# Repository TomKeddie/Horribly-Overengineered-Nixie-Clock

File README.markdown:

# Horribly Overengineered Nixie Clock

This is a "horribly overengineered" Nixie clock as the "clock" part could have been achieved far cheaper
and far easier. However, the end result (that there is an actual physical clock) is merely a side effect;
the main motivation for me was to use this project as means to learn something new. To this end, I've used
a fairly expensive ARM microcontroller and the mainboard also includes both USB and Ethernet connectivity.

There are two PCBs in this project: a driver board housing two Nixie tubes with their corresponding drivers
and a mainboard with the uC and other circuitry. The driver board is designed to fit into the 5x5 cm limit
and the mainboard fits the 5x10 cm limit of ITead Studio/Seeed Studio. A full kit with 6 digits would consist
of one mainboard PCB and three driver PCBs.

(The firmware will appear here as soon as there is something usable.)

## BOM

The key components are:

  * ИН-12 Nixie tubes
  * К155ИД1 drivers
  * [Taylor Electronics HVPS-V](http://www.tayloredge.com/storefront/SmartNixie/PSU/index.html) high voltage power supply
  * [NXP LPC1764](http://ics.nxp.com/products/lpc1000/lpc17xx/~LPC1764/) ARM Cortex-M3 microcontroller

Rev A:
  * [Micrel KSZ8001L](http://www.micrel.com/page.do?page=product-info/fastether_trans.jsp) Ethernet PHY

Rev B:
 
  * [Micrel MIC4680](http://micrel.com/index.php/en/component/joodb/article/41-step-down-internal-switches/24-mic4680.html) buck regulator
  * [Micrel KSZ8051RNL](http://micrel.com/index.php/en/component/joodb/article/13-phys/10-ksz8051rnl.html) Ethernet PHY

## Truth table for module

Note that for ease of routing the truth table doesn't match 74(1)41/K155ID1:

<table>
  <tr><th>Num</th> <th>A</th> <th>B</th> <th>C</th> <th>D</th></tr>
  <tr><td>0</td><td>H</td><td>L</td><td>H</td><td>L</td></tr>
  <tr><td>1</td><td>H</td><td>L</td><td>L</td><td>H</td></tr>
  <tr><td>2</td><td>L</td><td>H</td><td>H</td><td>L</td></tr>
  <tr><td>3</td><td>H</td><td>H</td><td>H</td><td>L</td></tr>
  <tr><td>4</td><td>L</td><td>H</td><td>L</td><td>L</td></tr>
  <tr><td>5</td><td>H</td><td>H</td><td>L</td><td>L</td></tr>
  <tr><td>6</td><td>L</td><td>L</td><td>H</td><td>L</td></tr>
  <tr><td>7</td><td>L</td><td>L</td><td>L</td><td>H</td></tr>
  <tr><td>8</td><td>L</td><td>L</td><td>L</td><td>L</td></tr>
  <tr><td>9</td><td>H</td><td>L</td><td>L</td><td>L</td></tr>
</table>

## Errata for Rev A

  * SWDCLK is not routed to JTAG. Oops.
  * P0[28] does not have an external pull-up. Note to self: read the datasheet. Twice.
  * Either LPC parts in general [do not like the cheap-o "tube" 32.768 kHz crystals](http://mbed.org/forum/mbed/topic/1110/) or 
    I can't figure out the proper load capacitance without an actual datasheet. Will switch to a SMD crystal if Rev B ever comes.
  * `RESET` was very flaky until I soldered a 1 μF capacitor to GND across it.
  * Ethernet chip went up in smoke. Oops.
  * No proper way to mount a heatsink on the 7805, and the HVPS audibly complains about low voltages that keep the heat of '05 in check.

## Changelog for Rev B

  * SWDCLK is properly routed.
  * Added a switch-mode 5V power supply based on [Micrel MIC4680](http://micrel.com/index.php/en/component/joodb/article/41-step-down-internal-switches/24-mic4680.html)
  * Changed the Ethernet PHY to [Micrel KSZ8051RNL](http://micrel.com/index.php/en/component/joodb/article/13-phys/10-ksz8051rnl.html)
  * Changed the RTC crystal
  * Added power and USB LEDs.

## Errata for Rev B

  * RTC still won't oscillate. I haven't given up on it yet, as I have a proper datasheet now.
  * Ethernet still doesn't work, but at least didn't go up in smoke. Might just be my bad soldering or a software issue.

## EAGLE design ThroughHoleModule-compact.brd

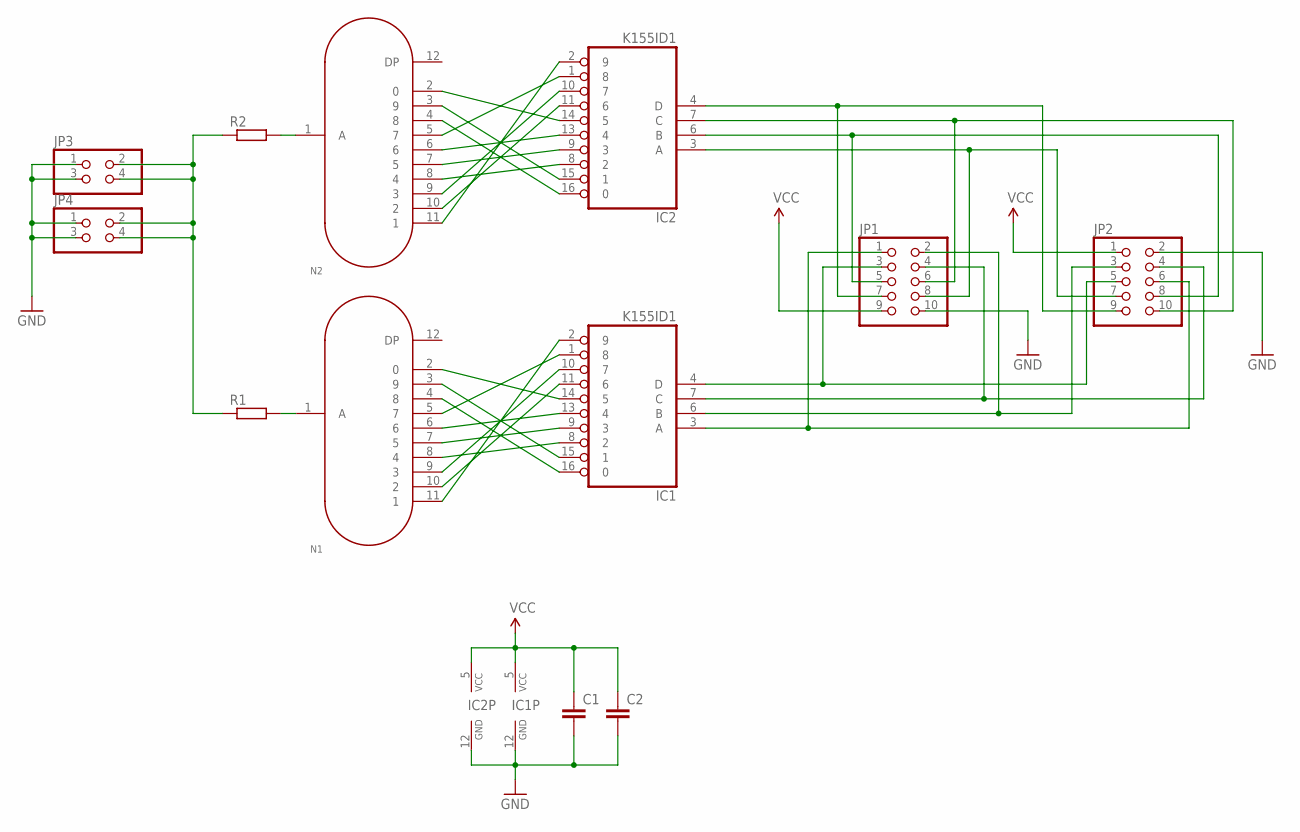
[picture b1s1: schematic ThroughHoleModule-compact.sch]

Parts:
C1, C2: C-EU050-030X075; C050-030X075
IC1, IC2: K155ID1; DIL16
JP1, JP2: PINHD-2X5; 2X05
JP3, JP4: PINHD-2X2; 2X02
N1, N2: IN-12B; IN-12
R1, R2: R-EU_0207/10; 0207/10

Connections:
1A: IC1.3 (A), JP1.1, JP2.6
1B: IC1.6 (B), JP1.2, JP2.3
1C: IC1.7 (C), JP1.4, JP2.4
1D: IC1.4 (D), JP1.3, JP2.5
2A: IC2.3 (A), JP1.8, JP2.7
2B: IC2.6 (B), JP1.5, JP2.8
2C: IC2.7 (C), JP1.6, JP2.10
2D: IC2.4 (D), JP1.7, JP2.9
GND: C1.2, C2.2, IC1.12 (GND), IC2.12 (GND), JP1.10, JP2.2, JP3.1, JP3.3, JP4.1, JP4.3
HV: JP3.2, JP3.4, JP4.2, JP4.4, R1.1, R2.1
unnamed: IC2.1 (8), N2.5 (7)
unnamed: IC2.13 (4), N2.6
unnamed: IC1.1 (8), N1.5 (7)
unnamed: IC1.13 (4), N1.6
unnamed: IC2.9 (3), N2.7 (5)
unnamed: IC2.8 (2), N2.8 (4)
unnamed: IC2.10 (7), N2.9 (3)
unnamed: IC2.11 (6), N2.10 (2)
unnamed: IC2.2 (9), N2.11 (1)
unnamed: IC2.14 (5), N2.2 (0)
unnamed: IC2.15 (1), N2.3 (9)
unnamed: IC2.16 (0), N2.4 (8)
unnamed: IC1.2 (9), N1.11 (1)
unnamed: IC1.11 (6), N1.10 (2)
unnamed: IC1.10 (7), N1.9 (3)
unnamed: IC1.8 (2), N1.8 (4)
unnamed: IC1.9 (3), N1.7 (5)
unnamed: IC1.16 (0), N1.4 (8)
unnamed: IC1.15 (1), N1.3 (9)
unnamed: IC1.14 (5), N1.2 (0)
unnamed: N1.1 (A), R1.2
unnamed: N2.1 (A), R2.2
VCC: C1.1, C2.1, IC1.5 (VCC), IC2.5 (VCC), JP1.9, JP2.1

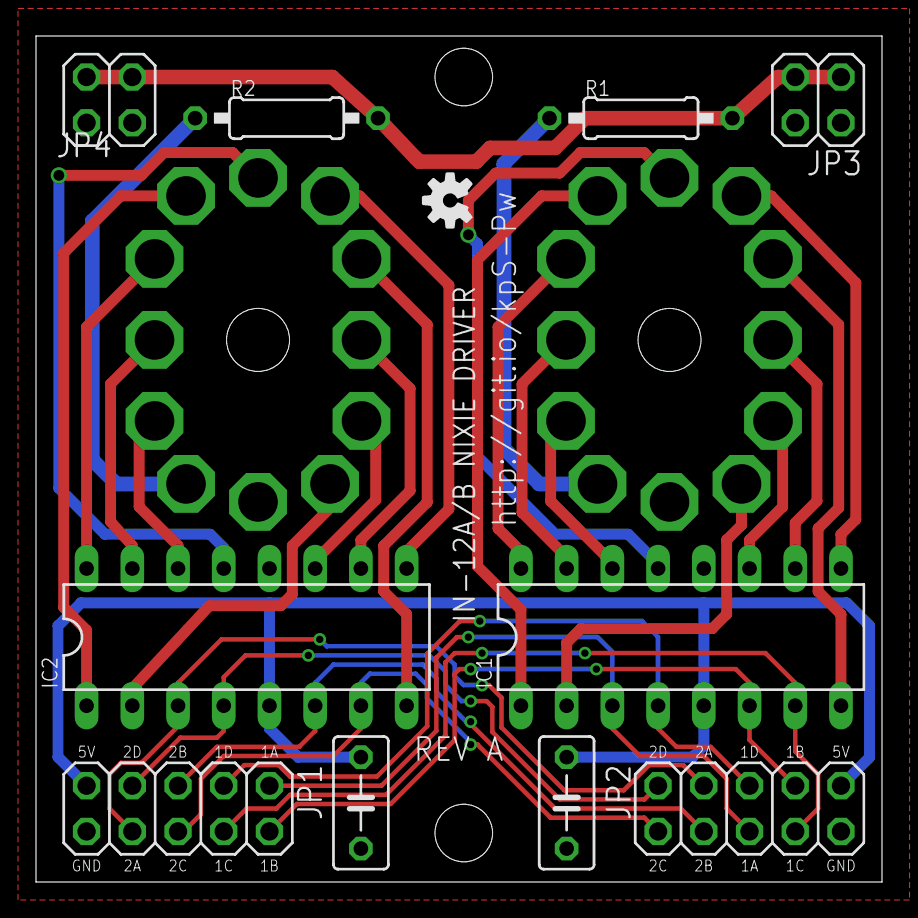
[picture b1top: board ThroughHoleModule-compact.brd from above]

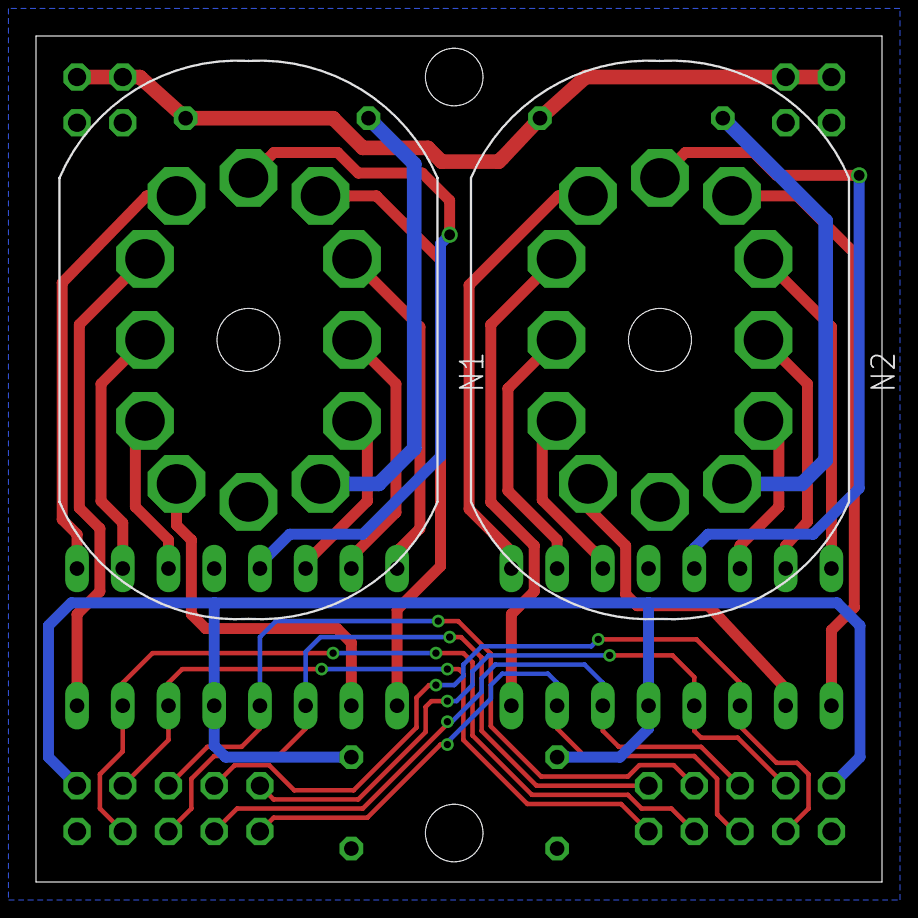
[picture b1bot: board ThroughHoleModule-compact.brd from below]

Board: 2 copper layers, 47.0 x 47.0 mm, 13 parts (2 on the bottom side), 33 nets.

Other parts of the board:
U$1: OSHW-LOGO-S

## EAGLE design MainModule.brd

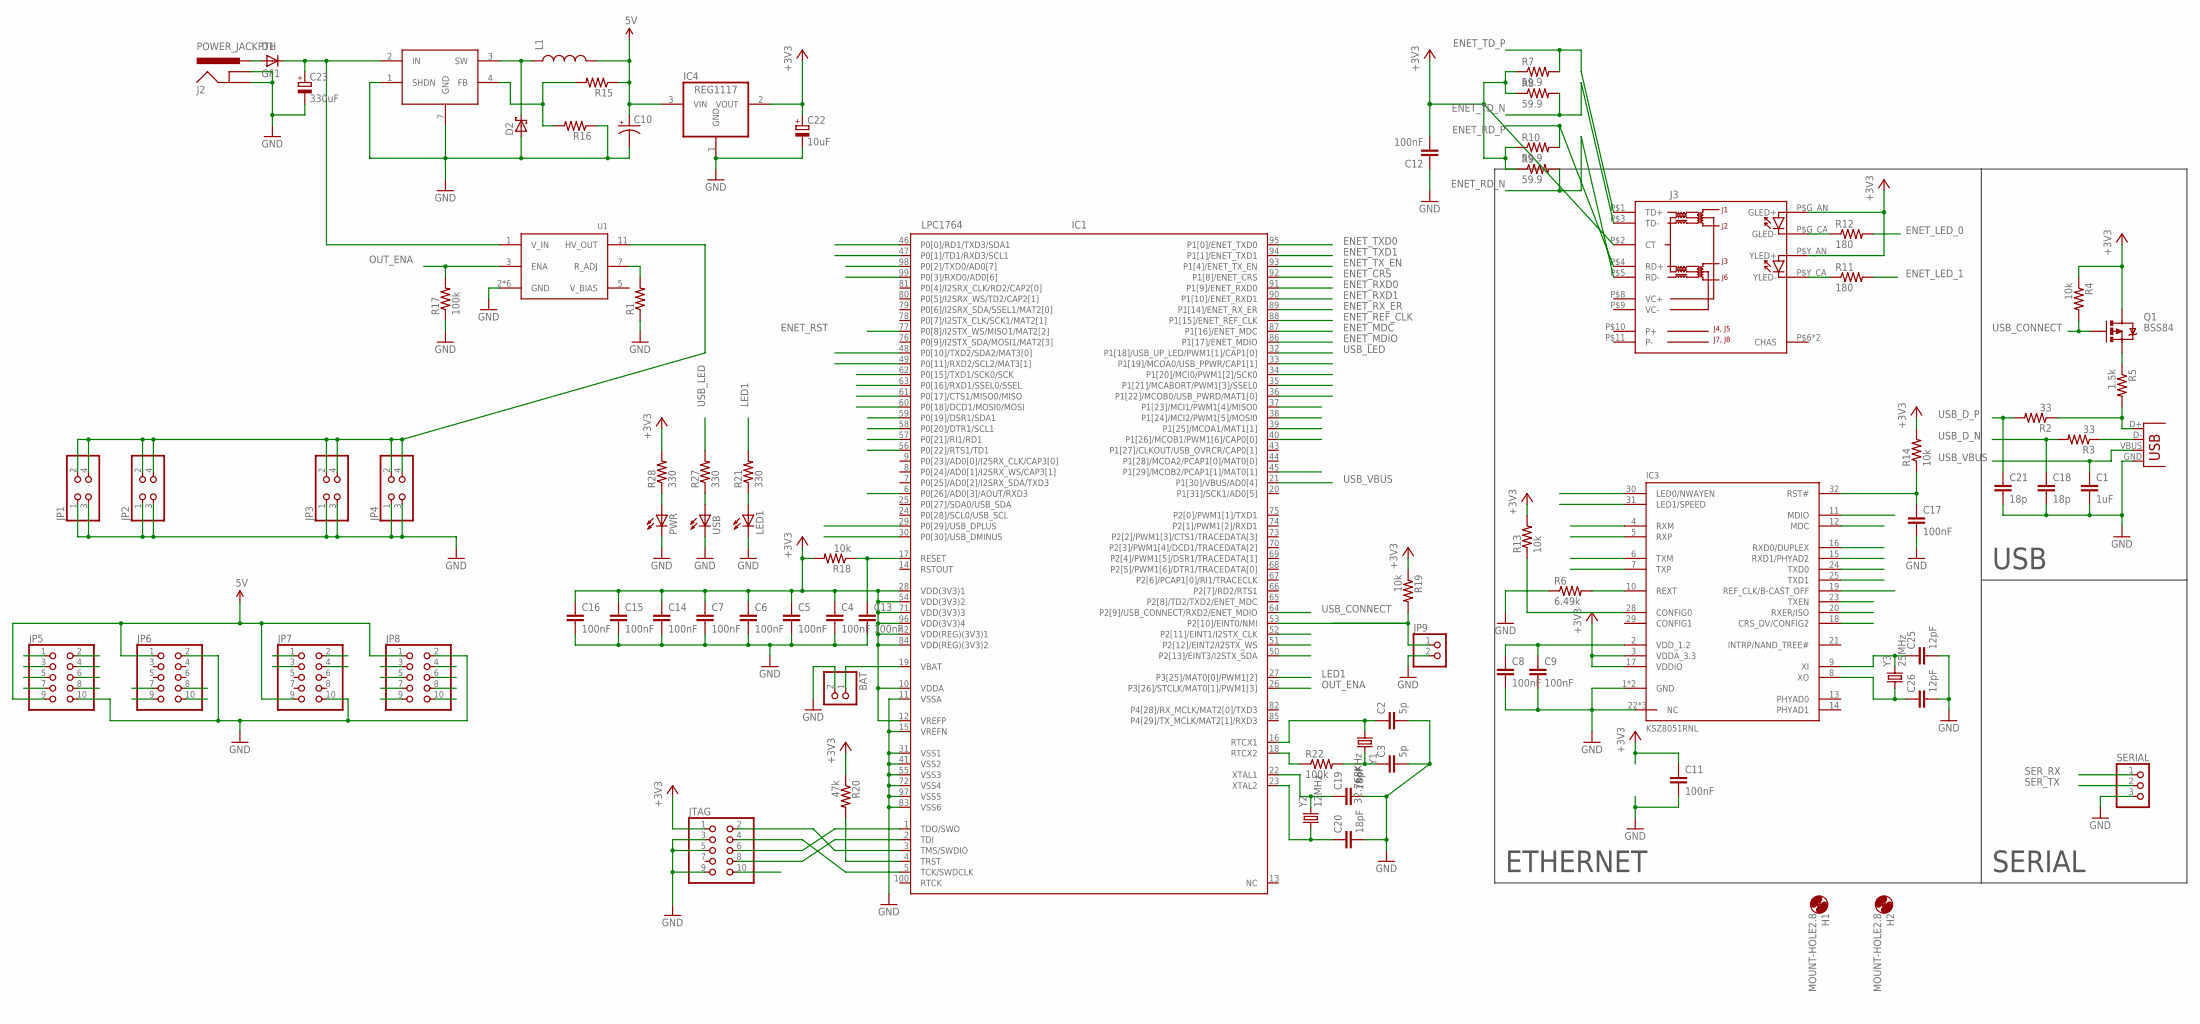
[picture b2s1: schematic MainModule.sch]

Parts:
BAT: PINHD-1X2; 1X02
C1: 1uF; 0805
C2, C3: 5p; 0805
C4, C5, C6, C7, C8, C9, C11, C12, C13, C14, C15, C16, C17: 100nF; 0805
C10: CAP_POLD; PANASONIC_D
C18, C21: 18p; 0805
C19, C20: 18pF; 0805
C22: 10uF; PANASONIC_B
C23: 330uF; E3,5-8
C25, C26: 12pF; 0805
D1: GF1; SMA-DO214AC
D2: SCHOTTKY-DIODESMD; SMB
H1, H2: MOUNT-HOLE2.8; 2,8
IC1: LPC1764; LQFP100-14X14
IC2: MIC4680; SOIC-8
IC3: KSZ8051RNL; QFN-32
IC4: REG1117; SOT223
J1: USBSMD; USB-MINIB
J2: POWER_JACKPTH; POWER_JACK_PTH
J3: MAGJACK-SI-52008; MAGJACK-SI-52008-F
JP1, JP2, JP3, JP4: PINHD-2X2; 2X02
JP5, JP6, JP7, JP8: PINHD-2X5; 2X05
JP9: PINHD-1X2; 1X02
JTAG: PINHD-2X5; 2X05
L1: INDUCTORB; INDUCTOR-MCSDC0906
LED1: LEDCHIP-LED0805; CHIP-LED0805
PWR: LEDCHIP-LED0805; CHIP-LED0805
Q1: BSS84; SOT23-3
R1, R15, R16: RESISTOR0805-RES; 0805
R2, R3: 33; 0805
R4, R13, R14, R18, R19: 10k; 0805
R5: 1.5k; 0805
R6: 6.49k; 0805
R7, R8, R9, R10: 59.9; 0805
R11, R12: 180; 0805
R17, R22: 100k; 0805
R20: 47k; 0805
R21, R27, R28: 330; 0805
SERIAL: PINHD-1X3; 1X03
U1: HVPS-1363
USB: LEDCHIP-LED0805; CHIP-LED0805
Y1: 32.768KHz; 85SMX
Y2: 12MHz; TXC-7A
Y3: 25MHz; TXC-7A

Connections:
5V: C10.+, IC4.3 (VIN), JP5.9, JP6.1, JP7.9, JP8.1, L1.4 (2), R15.1
+3V3: C4.1, C5.1, C6.1, C7.1, C11.1, C12.2, C14.1, C15.1, C16.1, C22.+, IC1.10 (VDDA), IC1.12 (VREFP), IC1.28 (VDD(3V3)1), IC1.42 (VDD(REG)(3V3)1), IC1.54 (VDD(3V3)2), IC1.71 (VDD(3V3)3), IC1.84 (VDD(REG)(3V3)2), IC1.96 (VDD(3V3)4), IC3.3 (VDDA_3.3), IC3.17 (VDDIO), IC4.2 (VOUT), J3.P$2 (CT), J3.P$G_AN (GLED+), J3.P$Y_AN (YLED+), JTAG.1, Q1.3 (D), R4.1, R7.1, R8.1, R9.1, R10.1, R13.2, R14.2, R18.2, R19.1, R20.1, R28.2
BTN1: IC1.45 (P1[29]/MCOB2/PCAP1[1]/MAT0[1])
ENET_CRS: IC1.92 (P1[8]/ENET_CRS), IC3.18 (CRS_DV/CONFIG2)
ENET_LED_0: IC3.30 (LED0/NWAYEN), R12.2
ENET_LED_1: IC3.31 (LED1/SPEED), R11.2
ENET_MDC: IC1.87 (P1[16]/ENET_MDC), IC3.12 (MDC)
ENET_MDIO: IC1.86 (P1[17]/ENET_MDIO), IC3.11 (MDIO)
ENET_RD_N: IC3.4 (RXM), J3.P$5 (RD-), R9.2
ENET_RD_P: IC3.5 (RXP), J3.P$4 (RD+), R10.2
ENET_REF_CLK: IC1.88 (P1[15]/ENET_REF_CLK), IC3.19 (REF_CLK/B-CAST_OFF)
ENET_RST: C17.1, IC1.77 (P0[8]/I2STX_WS/MISO1/MAT2[2]), IC3.32 (RST#), R14.1
ENET_RXD0: IC1.91 (P1[9]/ENET_RXD0), IC3.16 (RXD0/DUPLEX)
ENET_RXD1: IC1.90 (P1[10]/ENET_RXD1), IC3.15 (RXD1/PHYAD2)
ENET_RX_ER: IC1.89 (P1[14]/ENET_RX_ER), IC3.20 (RXER/ISO)
ENET_TD_N: IC3.6 (TXM), J3.P$3 (TD-), R8.2
ENET_TD_P: IC3.7 (TXP), J3.P$1 (TD+), R7.2
ENET_TXD0: IC1.95 (P1[0]/ENET_TXD0), IC3.24 (TXD0)
ENET_TXD1: IC1.94 (P1[1]/ENET_TXD1), IC3.25 (TXD1)
ENET_TX_EN: IC1.93 (P1[4]/ENET_TX_EN), IC3.23 (TXEN)
GND: BAT.2, C1.2, C2.2, C3.2, C4.2, C5.2, C6.2, C7.2, C8.2, C9.2, C10.-, C11.2, C12.1, C13.2, C14.2, C15.2, C16.2, C17.2, C18.2, C19.2, C20.2, C21.2, C22.-, C23.-, C25.2, C26.2, D2.A, IC1.11 (VSSA), IC1.15 (VREFN), IC1.31 (VSS1), IC1.41 (VSS2), IC1.55 (VSS3), IC1.72 (VSS4), IC1.83 (VSS6), IC1.97 (VSS5), IC2.1 (SHDN), IC2.5 (GND), IC2.6 (GND), IC2.7 (GND), IC2.8 (GND), IC3.1 (GND), IC3.22 (NC), IC3.26 (NC), IC3.27 (NC), IC3.EP (GND), IC4.1 (GND), J1.GND, J2.GND, J2.GNDBREAK, JP1.1, JP1.3, JP2.1, JP2.3, JP3.1, JP3.3, JP4.1, JP4.3, JP5.10, JP6.2, JP7.10, JP8.2, JP9.2, JTAG.3, JTAG.5, JTAG.9, LED1.C, PWR.C, R1.1, R6.1, R16.1, R17.1, SERIAL.3, U1.2 (GND), U1.4 (GND), U1.6 (GND), U1.8 (GND), U1.9 (GND), U1.10 (GND), USB.C
HV: JP1.2, JP1.4, JP2.2, JP2.4, JP3.2, JP3.4, JP4.2, JP4.4, U1.11 (HV_OUT)
JP5_1: IC1.33 (P1[19]/MCOA0/USB_PPWR/CAP1[1]), JP5.1
JP5_2: IC1.34 (P1[20]/MCI0/PWM1[2]/SCK0), JP5.2
JP5_3: IC1.35 (P1[21]/MCABORT/PWM1[3]/SSEL0), JP5.3
JP5_4: IC1.36 (P1[22]/MCOB0/USB_PWRD/MAT1[0]), JP5.4
JP5_5: IC1.37 (P1[23]/MCI1/PWM1[4]/MISO0), JP5.5
JP5_6: IC1.38 (P1[24]/MCI2/PWM1[5]/MOSI0), JP5.6
JP5_7: IC1.39 (P1[25]/MCOA1/MAT1[1]), JP5.7
JP5_8: IC1.40 (P1[26]/MCOB1/PWM1[6]/CAP0[0]), JP5.8
JP6_7: IC1.46 (P0[0]/RD1/TXD3/SDA1), JP6.7
JP6_8: IC1.48 (P0[10]/TXD2/SDA2/MAT3[0]), JP6.8
JP6_9: IC1.47 (P0[1]/TD1/RXD3/SCL1), JP6.9
JP6_10: IC1.49 (P0[11]/RXD2/SCL2/MAT3[1]), JP6.10
JP7_5: IC1.52 (P2[11]/EINT1/I2STX_CLK), JP7.1
JP7_6: IC1.50 (P2[13]/EINT3/I2STX_SDA), JP7.2
JP7_7: IC1.53 (P2[10]/EINT0/NMI), JP7.3, JP9.1, R19.2
JP7_8: IC1.51 (P2[12]/EINT2/I2STX_WS), JP7.4
JP8_3: IC1.57 (P0[21]/RI1/RD1), JP8.3
JP8_4: IC1.56 (P0[22]/RTS1/TD1), JP8.4
JP8_5: IC1.59 (P0[19]/DSR1/SDA1), JP8.5
JP8_6: IC1.58 (P0[20]/DTR1/SCL1), JP8.6
JP8_7: IC1.61 (P0[17]/CTS1/MISO0/MISO), JP8.7
JP8_8: IC1.60 (P0[18]/DCD1/MOSI0/MOSI), JP8.8
JP8_9: IC1.63 (P0[16]/RXD1/SSEL0/SSEL), JP8.9
JP8_10: IC1.62 (P0[15]/TXD1/SCK0/SCK), JP8.10
LED1: IC1.27 (P3[25]/MAT0[0]/PWM1[2]), R21.2
unnamed: R1.2, U1.7 (R_ADJ)
unnamed: C23.+, D1.K (C), IC2.2 (IN), U1.1 (V_IN)
unnamed: J1.D+, R2.1, R5.2
unnamed: R27.1, USB.A
unnamed: J1.D-, R3.1
unnamed: Q1.2 (S), R5.1
unnamed: PWR.A, R28.1
unnamed: C2.1, IC1.16 (RTCX1), Y1.1
unnamed: C3.1, R22.2, Y1.4 (2)
unnamed: IC3.10 (REXT), R6.2
unnamed: J3.P$G_CA (GLED-), R12.1
unnamed: C25.1, IC3.9 (XI), Y3.P$2 (2)
unnamed: J3.P$Y_CA (YLED-), R11.1
unnamed: C26.1, IC3.8 (XO), Y3.P$1 (1)
unnamed: IC1.4 (TRST), R20.2
unnamed: C8.1, C9.1, IC3.2 (VDD_1.2)
unnamed: C20.1, IC1.23 (XTAL2), Y2.P$1 (1)
unnamed: C19.1, IC1.22 (XTAL1), Y2.P$2 (2)
unnamed: D1.A, J2.PWR
unnamed: BAT.1, IC1.19 (VBAT)
unnamed: IC3.28 (CONFIG0), R13.1
unnamed: LED1.A, R21.1
unnamed: IC2.4 (FB), R15.2, R16.2
unnamed: D2.C, IC2.3 (SW), L1.1
unnamed: IC1.18 (RTCX2), R22.1
OUT_ENA: IC1.26 (P3[26]/STCLK/MAT0[1]/PWM1[3]), R17.2, U1.3 (ENA)
RESET: C13.1, IC1.17 (RESET), JTAG.10, R18.1
RSTOUT: IC1.6 (P0[26]/AD0[3]/AOUT/RXD3)
SER_RX: IC1.99 (P0[3]/RXD0/AD0[6]), SERIAL.1
SER_TX: IC1.98 (P0[2]/TXD0/AD0[7]), SERIAL.2
SWDCLK: IC1.5 (TCK/SWDCLK), JTAG.4
SWDIO: IC1.3 (TMS/SWDIO), JTAG.2
SWO: IC1.1 (TDO/SWO), JTAG.6
TDI: IC1.2 (TDI), JTAG.8
USB_CONNECT: IC1.64 (P2[9]/USB_CONNECT/RXD2/ENET_MDIO), Q1.1 (G), R4.2
USB_D_N: C18.1, IC1.30 (P0[30]/USB_DMINUS), R3.2
USB_D_P: C21.1, IC1.29 (P0[29]/USB_DPLUS), R2.2
USB_LED: IC1.32 (P1[18]/USB_UP_LED/PWM1[1]/CAP1[0]), R27.2
USB_VBUS: C1.1, IC1.21 (P1[30]/VBUS/AD0[4]), J1.VBUS

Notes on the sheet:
USB
ETHERNET
SERIAL

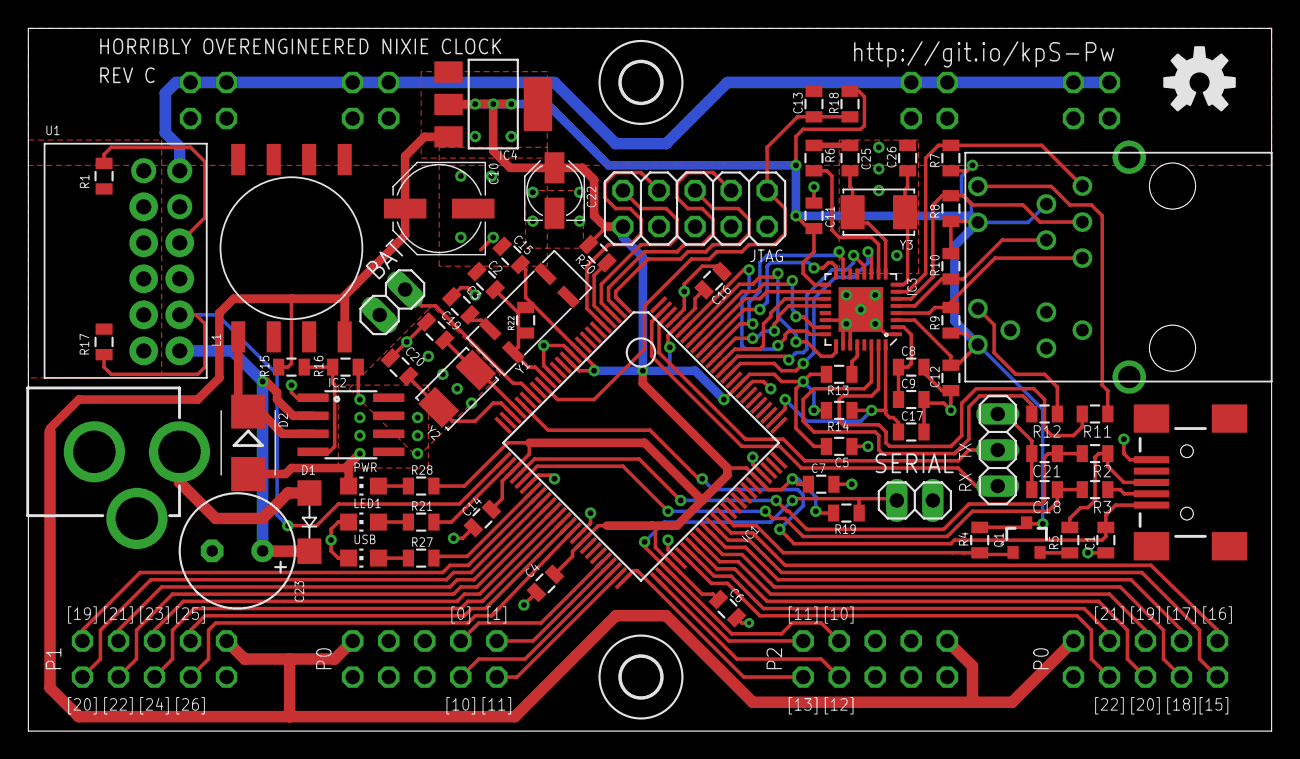
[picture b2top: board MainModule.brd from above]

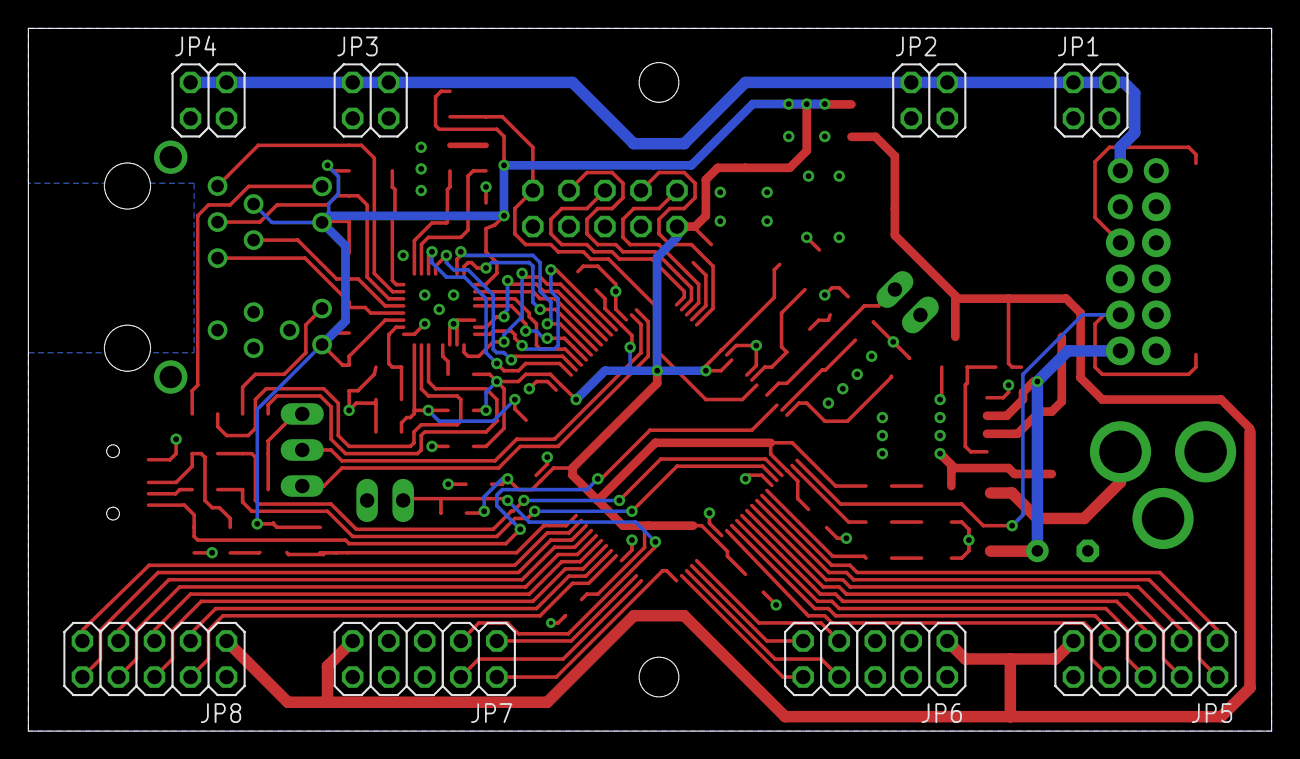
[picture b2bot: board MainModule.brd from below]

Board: 2 copper layers, 87.6 x 49.5 mm, 82 parts (8 on the bottom side), 84 nets.

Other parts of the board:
U$1: OSHW-LOGO-M

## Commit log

2012-02-26 added README
2012-02-28 manufacture-ready
2012-03-23 truth table
2012-03-31 errata
2012-04-07 RESET wants a capacitor
2012-10-12 Rev B
2017-01-29 Enlarged IN-12 mounting holes
2017-01-29 Reduced size for panelisation

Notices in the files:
parts and their libraries:
SparkFun: Licensing: CC v3.0 Share-Alike You are welcome to use this library for commercial purposes.
